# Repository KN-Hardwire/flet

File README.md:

# Electronic Flute
This repository holds hardware schematics and software for KN HARDWIRE Electronic Flute project.

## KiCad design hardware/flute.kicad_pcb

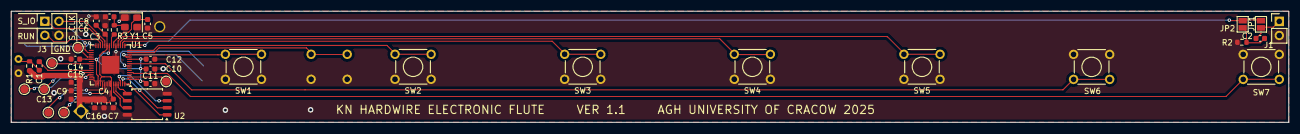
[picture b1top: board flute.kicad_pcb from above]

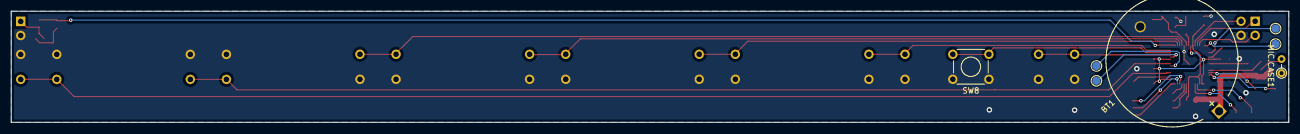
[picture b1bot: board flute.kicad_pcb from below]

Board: 2 copper layers, 230.0 x 20.0 mm, 47 parts (7 on the bottom side), 39 nets.

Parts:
BT1: Battery_Cell; BatteryHolder_MYOUNG_BS-07-A1BJ001_CR2032
C1, C2, C3, C10: 1uF; C_0603_1608Metric
C4, C7, C8, C9, C11, C12, C13, C14, C15, C16: 0.1uF; C_0603_1608Metric
C5, C6: 15pF; C_0603_1608Metric
J1: Conn_01x02; PinHeader_1x02_P2.54mm_Vertical
J3: Conn_01x04; PinHeader_2x02_P2.54mm_Vertical
JP1: COUPLING; SolderJumper-2_P1.3mm_Open_Pad1.0x1.5mm
JP2: NO_COUPLING; SolderJumper-2_P1.3mm_Open_Pad1.0x1.5mm
MIC.CASE1: R; R_Axial_DIN0204_L3.6mm_D1.6mm_P2.54mm_Vertical
R1: 2.2K; R_0603_1608Metric
R2: 100k; R_0603_1608Metric
R3: 1k; R_0603_1608Metric
SW1: C; SW_TH_Tactile_Omron_B3F-100x
SW2: D; SW_TH_Tactile_Omron_B3F-100x
SW3: E; SW_TH_Tactile_Omron_B3F-100x
SW4: F; SW_TH_Tactile_Omron_B3F-100x
SW5: G; SW_TH_Tactile_Omron_B3F-100x
SW6: A; SW_TH_Tactile_Omron_B3F-100x
SW7: H; SW_TH_Tactile_Omron_B3F-100x
SW8: OCTAVE?; SW_TH_Tactile_Omron_B3F-100x
TP2, TP3, TP4, TP5, TP6, TP7, TP8, TP9, TP10, TP11, TP12: TestPoint; TestPoint_Pad_D1.5mm
U1: RP2040; QFN-56-1EP_7x7mm_P0.4mm_EP3.2x3.2mm
U2: W25Q128JVS; SOIC-8_5.3x5.3mm_P1.27mm
Y1: Crystal_GND24; Crystal_SMD_Abracon_ABM8G-4Pin_3.2x2.5mm

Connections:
+1V1: C3.2, C7.1, C8.1, U1.23 (DVDD), U1.45 (VREG_VOUT), U1.50 (DVDD)
+3V3: BT1.1 (+), C4.1, C9.1, C10.1, C11.1, C12.1, C13.1, C14.1, C15.1, C16.1, R1.2, U1.1 (IOVDD), U1.10 (IOVDD), U1.22 (IOVDD), U1.33 (IOVDD), U1.42 (IOVDD), U1.43 (ADC_AVDD), U1.44 (VREG_IN), U1.48 (USB_VDD), U1.49 (IOVDD)
/KEY_A: SW6.2, U1.8 (GPIO6)
/KEY_C: SW1.2, U1.12 (GPIO9)
/KEY_D: SW2.2, U1.14 (GPIO11)
/KEY_E: SW3.2, U1.16 (GPIO13)
/KEY_F: SW4.2, U1.17 (GPIO14)
/KEY_G: SW5.2, U1.18 (GPIO15)
/KEY_H: SW7.2, U1.4 (GPIO2)
/KEY_OCTAVE: SW8.2, U1.13 (GPIO10)
/MIC_OUTPUT: C1.2, U1.38 (GPIO26_ADC0)
/PWM_OUT: JP1.2 (B), JP2.2 (B), U1.15 (GPIO12)
/RASPBERRY_PI_PICO/QSPI_CS: U1.56 (QSPI_SS), U2.1 (~CS)
/RASPBERRY_PI_PICO/QSPI_SCLK: U1.52 (QSPI_SCLK), U2.6 (CLK)
/RASPBERRY_PI_PICO/QSPI_SD0: U1.53 (QSPI_SD0), U2.5 (DI/IO_{0})
/RASPBERRY_PI_PICO/QSPI_SD1: U1.55 (QSPI_SD1), U2.2 (DO/IO_{1})
/RASPBERRY_PI_PICO/QSPI_SD2: U1.54 (QSPI_SD2), U2.3 (~WP/IO_{2})
/RASPBERRY_PI_PICO/QSPI_SD3: U1.51 (QSPI_SD3), U2.7 (~HOLD/~RESET/IO_{3})
/RASPBERRY_PI_PICO/RUN: J3.3, U1.26 (RUN)
/RASPBERRY_PI_PICO/SWCLK: J3.2, U1.24 (SWCLK)
/RASPBERRY_PI_PICO/SWDIO: J3.1, U1.25 (SWD)
/RASPBERRY_PI_PICO/USB_DM: TP4.1, U1.46 (USB_DM)
/RASPBERRY_PI_PICO/USB_DP: TP3.1, U1.47 (USB_DP)
/RASPBERRY_PI_PICO/XIN: C5.1, U1.20 (XIN), Y1.1
/RASPBERRY_PI_PICO/XOUT: R3.1, U1.21 (XOUT)
GND: BT1.2 (-), C3.1, C4.2, C5.2, C6.2, C7.2, C8.2, C9.2, C10.2, C11.2, C12.2, C13.2, C14.2, C15.2, C16.2, J1.2, J3.4, MIC.CASE1.1, R2.2, SW1.1, SW2.1, SW3.1, SW4.1, SW5.1, SW6.1, SW7.1, SW8.1, U1.19 (TESTEN), U1.57 (GND), U2.4 (GND), U2.8 (VCC), Y1.2, Y1.4
unnamed: C1.1, MIC.CASE1.2, R1.1
unnamed: C6.1, R3.2, Y1.3
unnamed: C2.1, J1.1, JP2.1 (A)
unnamed: C2.2, JP1.1 (A), R2.1
unnamed: TP2.1, U1.2 (GPIO0)
unnamed: TP5.1, U1.7 (GPIO5)
unnamed: TP6.1, U1.11 (GPIO8)
unnamed: TP7.1, U1.28 (GPIO17)
unnamed: TP8.1, U1.30 (GPIO19)
unnamed: TP9.1, U1.32 (GPIO21)
unnamed: TP10.1, U1.35 (GPIO23)
unnamed: TP11.1, U1.39 (GPIO27_ADC1)
unnamed: TP12.1, U1.40 (GPIO28_ADC2)

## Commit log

2025-10-28 initial
2025-10-29 minor changes
2025-10-29 add handling buttons
2025-11-03 change output to 1 pin
2025-11-04 szpont
2025-11-05 clean up
2025-11-05 prototyping
2025-11-11 adjust variable types for embedded standard
2025-11-11 change project hierarchy
2025-11-11 gitingnore for kicad
2025-11-11 initial schematic
2025-11-11 pcb outline
2025-11-11 r and c footprint change
2025-11-12 move readme
2025-11-14 Poprawa makr
2025-11-14 minor schematic changes
2025-11-14 modularize
2025-11-14 output filter added
2025-11-14 raspberry pi pcb
2025-11-14 added missing connection to QSPI_SD2
2025-11-15 aligned button + new pcb outline
2025-11-15 added jack and battery
2025-11-15 added #auto_saved_files# to gitignore
2025-11-15 OCTAVE button moved to the pcb bottom
2025-11-15 buttons added to the pcb
2025-11-15 pcb connections corrected
2025-11-15 zonefills for pcb
2025-11-15 type of connections changed
2025-11-16 complete pcb ver1
2025-11-16 add pico-sdk as submodule
2025-11-19 add automatic build test
2025-11-19 fix workflow
2025-11-21 prototyping with microphone values, calculating differentials
2025-11-22 change global variables to static, remove redundant function
2025-11-23 calculate volume from diff count
2025-11-27 adjust output volume for logarithmic scale
2025-11-27 build for pico instead of pico_w
2025-11-28 test points added to the schematic
2025-11-28 first part of test points placed on pcb
2025-11-28 test points placed on the pcb
2025-11-28 saved changes
2025-11-29 output coupling solder jumpers for schematic
2025-11-29 minor corrections
2025-12-02 errors with elements placement corrected
2025-12-02 error with PWM_OUT corrected
2025-12-02 problem with soldermask corrected
2025-12-02 pcb ver1.1
2025-12-03 complete pcb ver1.1
2025-12-05 avoid recursion in mask/frequency functions
2025-12-14 Rename project
2025-12-23 Add central types.h with PROJECT_VARIANT macros
2025-12-23 Add necessary changes in functions to match PROJECT_VARIANT macros
2025-12-23 Fix: types.h compilation errors
2025-12-23 Fix: functions.h compilation errors
2025-12-23 minor stylistic changes, fix warning
2025-12-23 add debug option to cmake
2025-12-23 fix in volume_to_duty
2025-12-25 Improve clarity of debug info
